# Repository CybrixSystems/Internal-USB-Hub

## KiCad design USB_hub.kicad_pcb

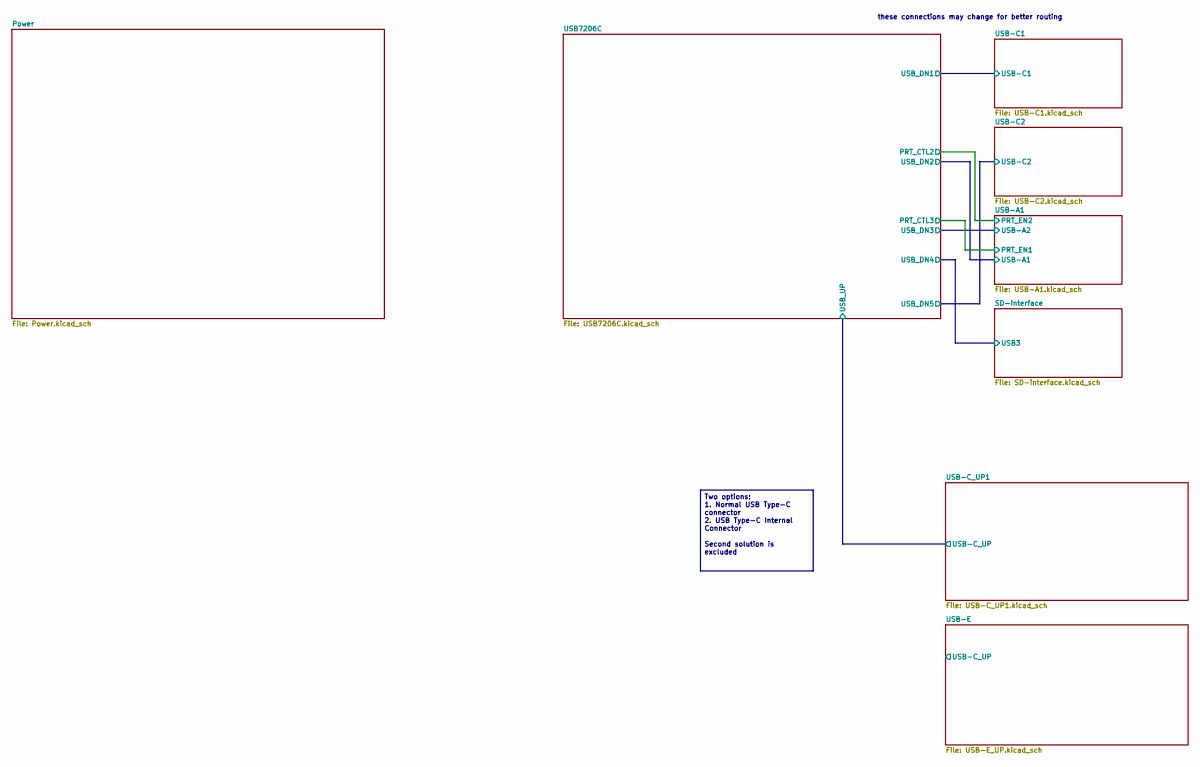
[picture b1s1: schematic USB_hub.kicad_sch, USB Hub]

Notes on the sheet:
these connections may change for better routing
Two options: 1. Normal USB Type-C connector 2. USB Type-C Internal Connector Second solution is excluded

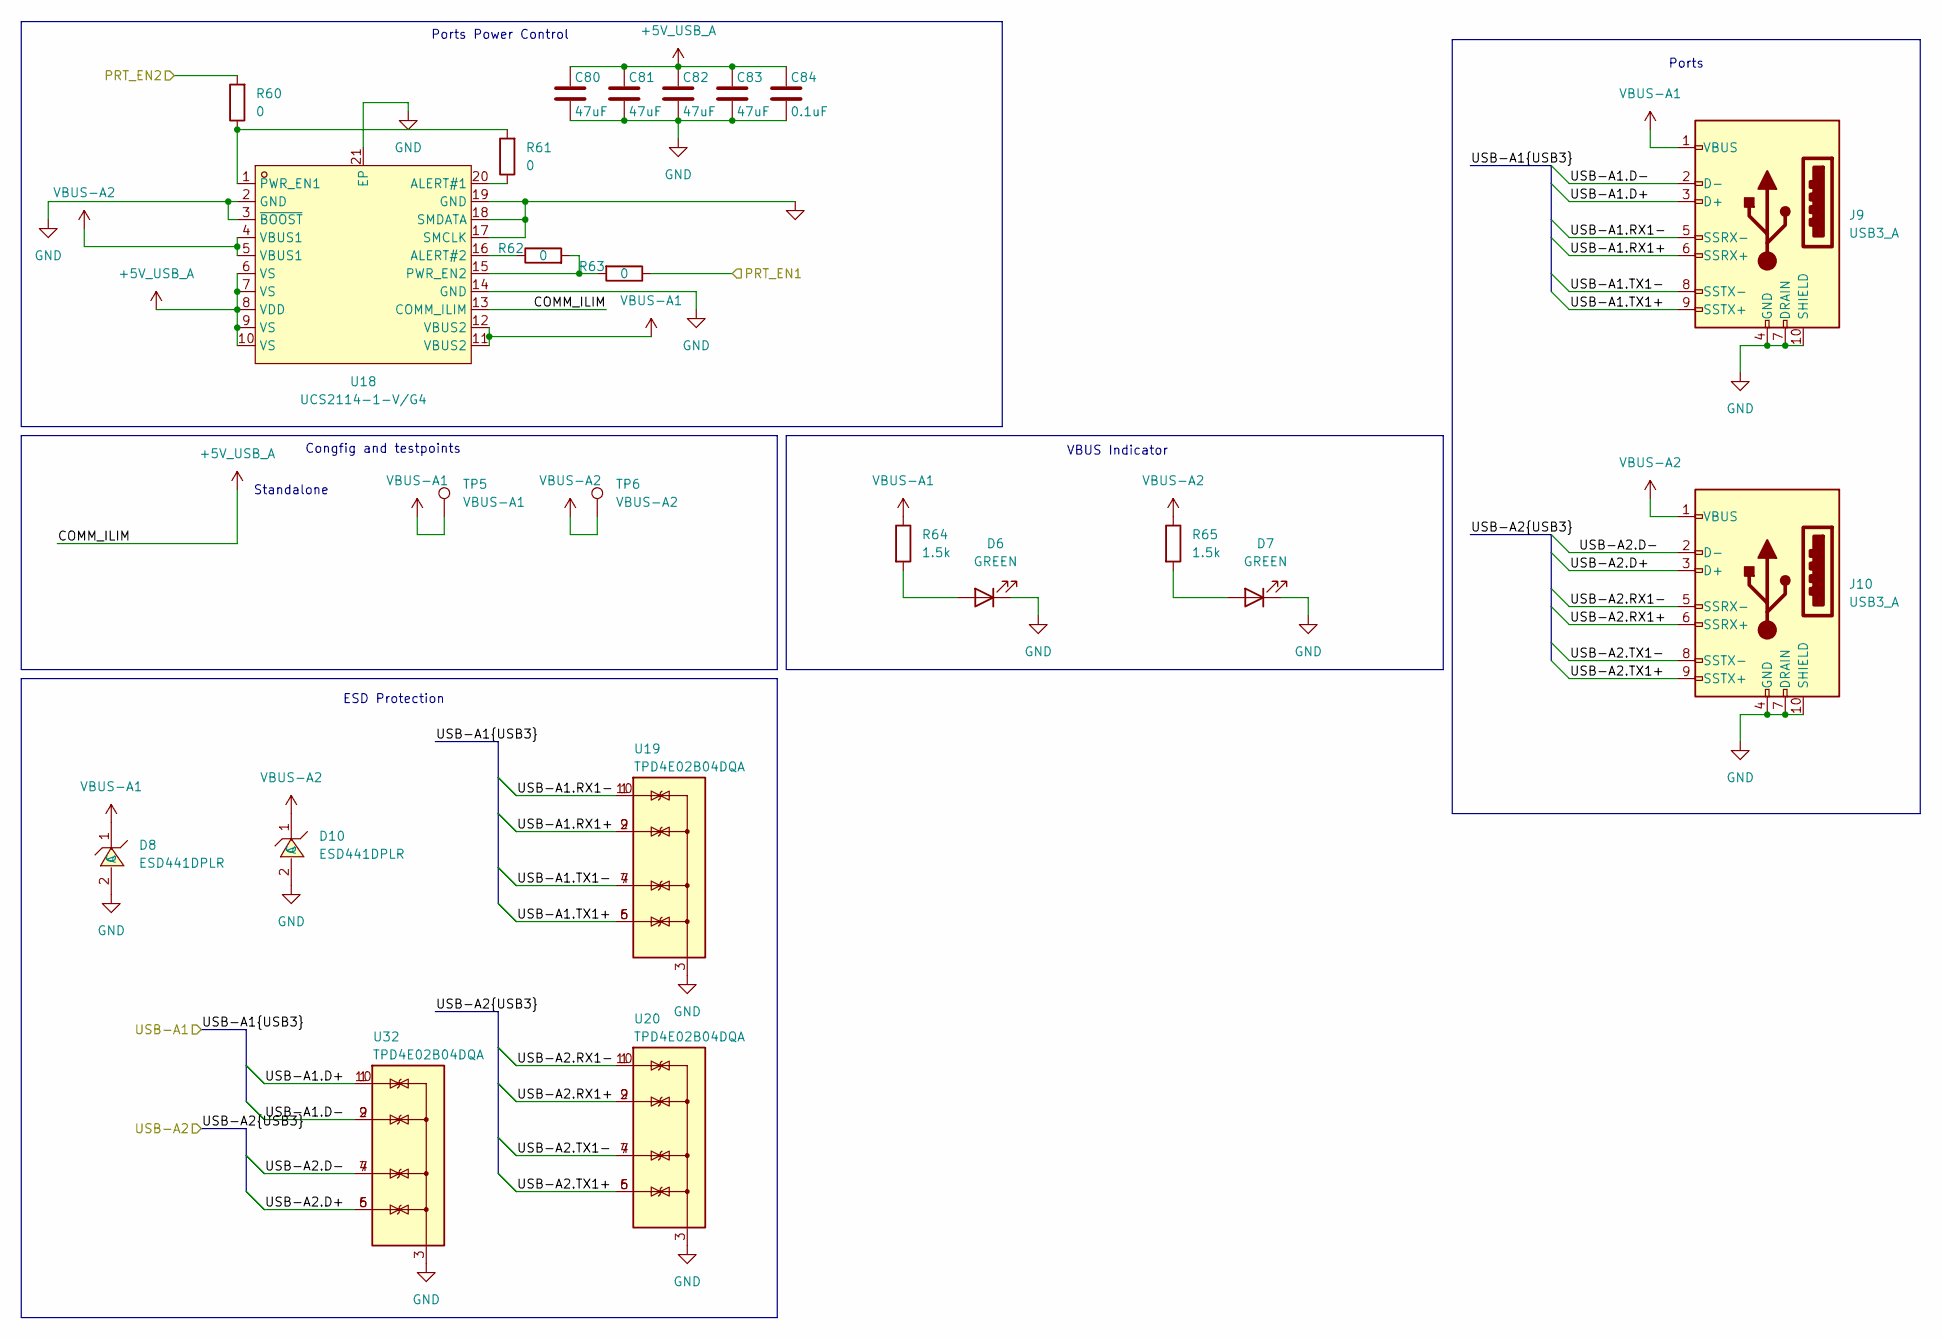
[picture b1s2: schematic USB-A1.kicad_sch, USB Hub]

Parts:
C80, C81, C82, C83: 47uF; C_Radial_D5.0mm_H11.0mm_P2.00mm; LCSC Part C721300
C84: 0.1uF; C_0201_0603Metric; LCSC Part C181043
D6, D7: GREEN; LED_0603_1608Metric; LCSC Part C22371298
D8, D10: ESD441DPLR; X2SON-2_L0.6-W0.3-P0.35; LCSC Part C22427765
J9, J10: USB3_A; GSB4116344HR; LCSC Part C5119948
R60, R61, R62, R63: 0; R_0603_1608Metric; LCSC Part C2906974
R64, R65: 1.5k; R_0402_1005Metric; LCSC Part C327253
TP5: VBUS-A1; TestPoint_Pad_D1.0mm
TP6: VBUS-A2; TestPoint_Pad_D1.0mm
U18: UCS2114-1-V/G4; QFN-20_L4.0-W4.0-P0.50-BL-EP2.7; Mouser Part No 579-UCS2114-1-V/LX; LCSC Part C638222
U19, U20, U32: TPD4E02B04DQA; USON-10_2.5x1.0mm_P0.5mm; LCSC Part C106794

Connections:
+5V_USB_A: C80.1, C81.1, C82.1, C83.1, C84.1, U18.6 (VS), U18.7 (VS), U18.8 (VDD), U18.9 (VS), U18.10 (VS), U18.13 (COMM_ILIM); also elsewhere on the board
/USB-A1/PRT_EN1: R63.1; also elsewhere on the board
/USB-A1/PRT_EN2: R60.2; also elsewhere on the board
/USB-A1/USB-A1.D+: J9.3 (D+), U32.1 (IO1), U32.10 (NC); also elsewhere on the board
/USB-A1/USB-A1.D-: J9.2 (D-), U32.2 (IO2), U32.9 (NC); also elsewhere on the board
/USB-A1/USB-A1.RX1+: J9.6 (SSRX+), U19.2 (IO2), U19.9 (NC); also elsewhere on the board
/USB-A1/USB-A1.RX1-: J9.5 (SSRX-), U19.1 (IO1), U19.10 (NC); also elsewhere on the board
/USB-A1/USB-A1.TX1+: J9.9 (SSTX+), U19.5 (IO4), U19.6 (NC); also elsewhere on the board
/USB-A1/USB-A1.TX1-: J9.8 (SSTX-), U19.4 (IO3), U19.7 (NC); also elsewhere on the board
/USB-A1/USB-A2.D+: J10.3 (D+), U32.5 (IO4), U32.6 (NC); also elsewhere on the board
/USB-A1/USB-A2.D-: J10.2 (D-), U32.4 (IO3), U32.7 (NC); also elsewhere on the board
/USB-A1/USB-A2.RX1+: J10.6 (SSRX+), U20.2 (IO2), U20.9 (NC); also elsewhere on the board
/USB-A1/USB-A2.RX1-: J10.5 (SSRX-), U20.1 (IO1), U20.10 (NC); also elsewhere on the board
/USB-A1/USB-A2.TX1+: J10.9 (SSTX+), U20.5 (IO4), U20.6 (NC); also elsewhere on the board
/USB-A1/USB-A2.TX1-: J10.8 (SSTX-), U20.4 (IO3), U20.7 (NC); also elsewhere on the board
GND: C80.2, C81.2, C82.2, C83.2, C84.2, D6.1 (K), D7.1 (K), D8.2 (A), D10.2 (A), J9.4 (GND), J9.7 (DRAIN), J9.10 (SHIELD), J10.4 (GND), J10.7 (DRAIN), J10.10 (SHIELD), U18.2 (GND), U18.3 (~BOOST), U18.14 (GND), U18.17 (SMCLK), U18.18 (SMDATA), U18.19 (GND), U18.21 (EP), U19.3 (G), U19.8 (G), U20.3 (G), U20.8 (G), U32.3 (G), U32.8 (G); also elsewhere on the board
unnamed: D6.2 (A), R64.2
unnamed: D7.2 (A), R65.2
unnamed: R61.1, U18.20 (ALERT#1)
unnamed: R62.1, U18.16 (ALERT#2)
unnamed: R60.1, R61.2, U18.1 (PWR_EN1)
unnamed: R62.2, R63.2, U18.15 (PWR_EN2)
VBUS-A1: D8.1 (C), J9.1 (VBUS), R64.1, TP5.1, U18.11 (VBUS2), U18.12 (VBUS2)
VBUS-A2: D10.1 (C), J10.1 (VBUS), R65.1, TP6.1, U18.4 (VBUS1), U18.5 (VBUS1)

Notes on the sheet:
ESD Protection
Standalone
Ports
Congfig and testpoints
VBUS Indicator
Ports Power Control

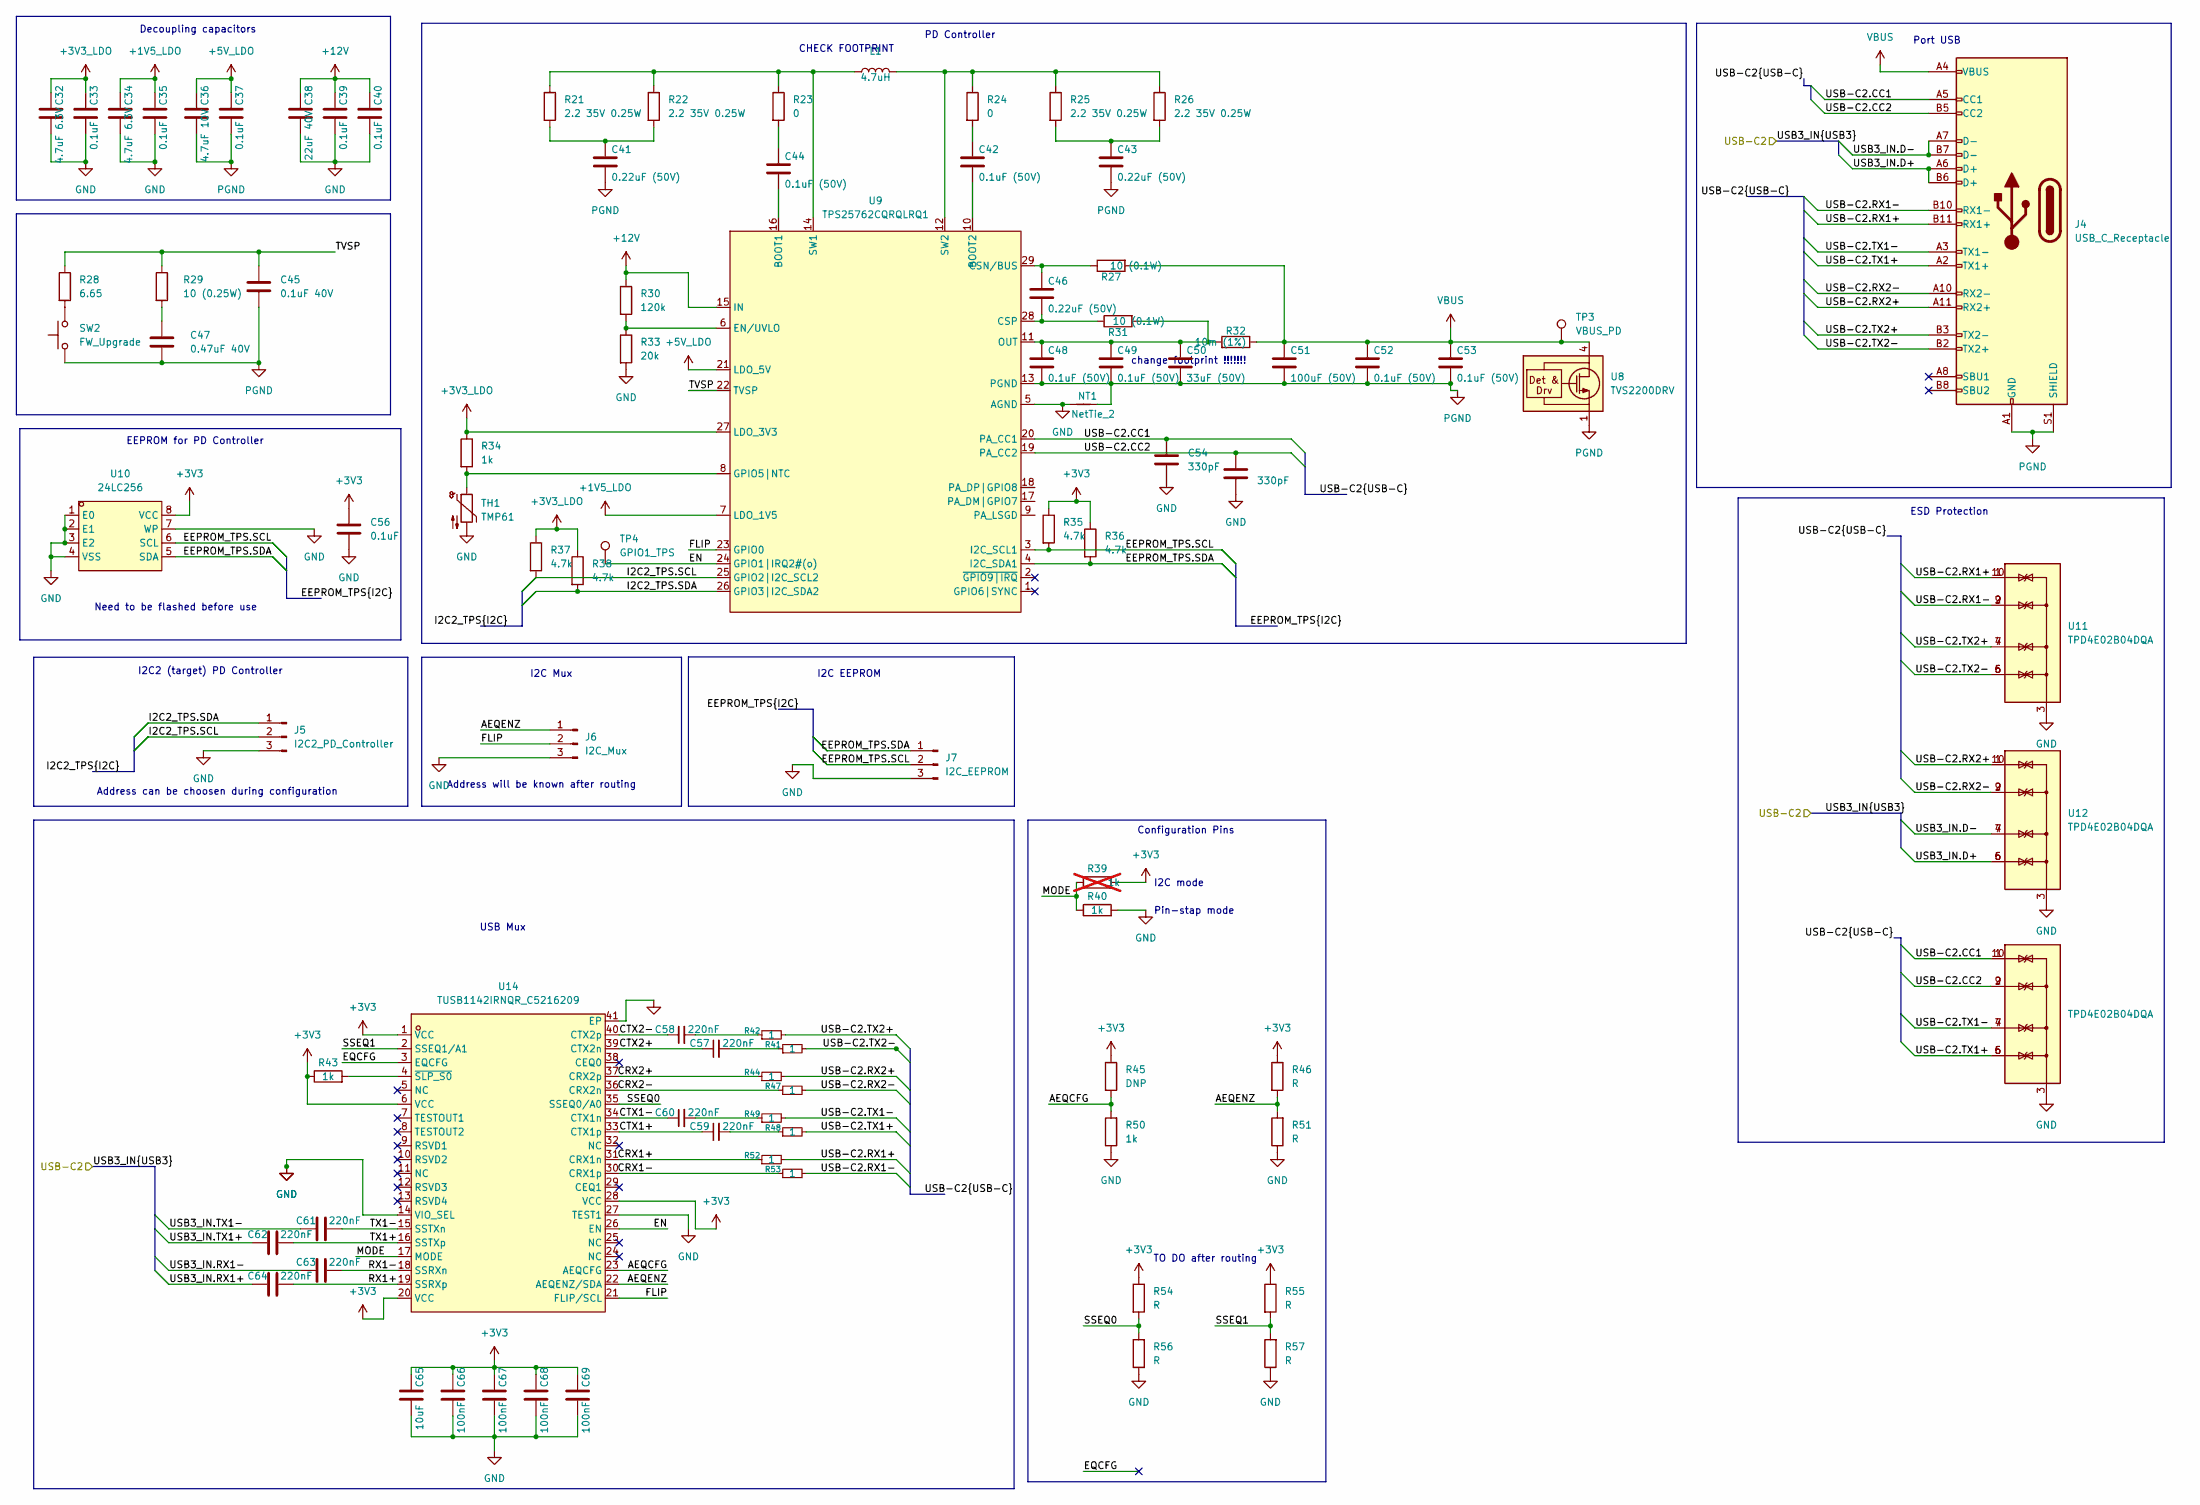
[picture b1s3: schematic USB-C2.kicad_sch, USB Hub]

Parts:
C32, C34: 4.7uF 6.3V; C_0402_1005Metric; LCSC Part C6119944
C33, C35, C37, C39, C40, C56: 0.1uF; C_0201_0603Metric; LCSC Part C181043
C36: 4.7uF 10V; C_0402_1005Metric; LCSC Part C6119944
C38: 22uF 40V; C_1812_4532Metric; LCSC Part C141660
C41, C43, C46: 0.22uF (50V); C_0402_1005Metric; LCSC Part C114401
C42, C44, C48, C49, C52, C53: 0.1uF (50V); C_0402_1005Metric; LCSC Part C5182432
C45: 0.1uF 40V; C_0402_1005Metric; LCSC Part C5182432
C47: 0.47uF 40V; C_0603_1608Metric; LCSC Part C513577
C50: 33uF (50V); C_2220_5750Metric; Mouser Part No 710-865080645010
C51: 100uF (50V); C_Radial_D6.3mm_H11.0mm_P2.50mm; LCSC Part C109392
C54, C55: 330pF; C_0402_1005Metric; LCSC Part C325463
C57, C58, C59, C60, C61, C62, C63, C64: 220nF; C_0201_0603Metric; LCSC Part C701263
C65: 10uF; C_0805_2012Metric; LCSC Part C3039694
C66, C67, C68, C69: 100nF; C_0201_0603Metric; LCSC Part C181043
J4: USB_C_Receptacle; USB420003A; Mouser Part No 640-USB4200-03-A
J5: I2C2_PD_Controller; PinHeader_1x03_P1.00mm_Vertical
J6: I2C_Mux; PinHeader_1x03_P1.00mm_Vertical
J7: I2C_EEPROM; PinHeader_1x03_P1.00mm_Vertical
L1: 4.7uH; L_Coilcraft_XAL1010-XXX; LCSC Part C18199458
NT1: NetTie_2; R_0603_1608Metric
R21, R22, R25, R26: 2.2 35V 0.25W; R_0603_1608Metric; LCSC Part C966185
R23, R24: 0; R_0603_1608Metric; LCSC Part C2906974
R27, R31: 10 (0.1W); R_0603_1608Metric; LCSC Part C510088
R28: 6.65; R_0402_1005Metric; Mouser Part No 71-CRCW04026R65FKEDH; LCSC Part C332644
R29: 10 (0.25W); R_0603_1608Metric; LCSC Part C510088
R30: 120k; R_0402_1005Metric; LCSC Part C93945
R32: 10m (1%); R_2010_5025Metric; LCSC Part C844898
R33: 20k; R_0402_1005Metric; LCSC Part C25765
R34, R40, R43, R50: 1k; R_0402_1005Metric; LCSC Part C11702
R35, R36, R37, R38: 4.7k; R_0402_1005Metric; LCSC Part C105871
R39: 1k; R_0402_1005Metric; LCSC Part C11702; not fitted
R41, R42, R44, R47, R48, R49, R52, R53: 1; R_0201_0603Metric; LCSC Part C469665
R45: DNP; R_0402_1005Metric
R46, R51, R54, R55, R56, R57: R; R_0402_1005Metric
SW2: FW_Upgrade; ultra_small_switch_1.6x3.0mm; LCSC Part C913788
TH1: TMP61; PinHeader_1x02_P1.27mm_Vertical
TP3: VBUS_PD; TestPoint_Pad_D1.0mm
TP4: GPIO1_TPS; TestPoint_Pad_D1.0mm
U8: TVS2200DRV; WSON-6-1EP_2x2mm_P0.65mm_EP1x1.6mm; LCSC Part C523793
U9: TPS25762CQRQLRQ1; VQFN-HR-29_L6.0-W5.0-P0.50_TPS25762CQRQLRQ1; Mouser Part No 595-TPS25762CQRQLRQ1; LCSC Part C5986888
U10: 24LC256; SO-8_L4.9-W3.9-P1.27-LS5.9-BL; LCSC Part C283433
U11, U12, U13: TPD4E02B04DQA; USON-10_2.5x1.0mm_P0.5mm; LCSC Part C106794
U14: TUSB1142IRNQR_C5216209; WQFN-40_L6.0-W4.0-P0.40-TL-EP; LCSC Part C5216209

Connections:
+1V5_LDO: C34.1, C35.1, U9.7 (LDO_1V5)
+3V3: C56.1, C65.1, C66.1, C67.1, C68.1, C69.1, R35.1, R36.1, R39.2, R43.1, R45.1, R46.1, R54.1, R55.1, U10.8 (VCC), U14.1 (VCC), U14.6 (VCC), U14.20 (VCC), U14.28 (VCC); also elsewhere on the board
+3V3_LDO: C32.1, C33.1, R34.1, R37.1, R38.1, U9.27 (LDO_3V3)
+5V_LDO: C36.1, C37.1, U9.21 (LDO_5V)
+12V: C38.1, C39.1, C40.1, R30.1, U9.15 (IN); also elsewhere on the board
/USB-C2/AEQCFG: R45.2, R50.2, U14.23 (AEQCFG)
/USB-C2/AEQENZ: J6.1, R46.2, R51.2, U14.22 (AEQENZ/SDA)
/USB-C2/CRX1+: R52.1, U14.31 (CRX1n)
/USB-C2/CRX1-: R53.1, U14.30 (CRX1p)
/USB-C2/CRX2+: R44.1, U14.37 (CRX2p)
/USB-C2/CRX2-: R47.1, U14.36 (CRX2n)
/USB-C2/CTX1+: C59.1, U14.33 (CTX1p)
/USB-C2/CTX1-: C60.1, U14.34 (CTX1n)
/USB-C2/CTX2+: C57.1, U14.39 (CTX2n)
/USB-C2/CTX2-: C58.1, U14.40 (CTX2p)
/USB-C2/EEPROM_TPS.SCL: J7.2, R35.2, U9.3 (I2C_SCL1), U10.6 (SCL)
/USB-C2/EEPROM_TPS.SDA: J7.1, R36.2, U9.4 (I2C_SDA1), U10.5 (SDA)
/USB-C2/EN: TP4.1, U9.24 (GPIO1|IRQ2#(o)), U14.26 (EN)
/USB-C2/EQCFG: U14.3 (EQCFG)
/USB-C2/FLIP: J6.2, U9.23 (GPIO0), U14.21 (FLIP/SCL)
/USB-C2/I2C2_TPS.SCL: J5.2, R37.2, U9.25 (GPIO2|I2C_SCL2)
/USB-C2/I2C2_TPS.SDA: J5.1, R38.2, U9.26 (GPIO3|I2C_SDA2)
/USB-C2/MODE: R39.1, R40.1, U14.17 (MODE)
/USB-C2/RX1+: C64.2, U14.19 (SSRXp)
/USB-C2/RX1-: C63.2, U14.18 (SSRXn)
/USB-C2/SSEQ0: R54.2, R56.2, U14.35 (SSEQ0/A0)
/USB-C2/SSEQ1: R55.2, R57.2, U14.2 (SSEQ1/A1)
/USB-C2/TVSP: C45.1, R28.1, R29.1, U9.22 (TVSP)
/USB-C2/TX1+: C62.2, U14.16 (SSTXp)
/USB-C2/TX1-: C61.2, U14.15 (SSTXn)
/USB-C2/USB3_IN.D+: J4.A6 (D+), J4.B6 (D+), U12.5 (IO4), U12.6 (NC); also elsewhere on the board
/USB-C2/USB3_IN.D-: J4.A7 (D-), J4.B7 (D-), U12.4 (IO3), U12.7 (NC); also elsewhere on the board
/USB-C2/USB3_IN.RX1+: C64.1; also elsewhere on the board
/USB-C2/USB3_IN.RX1-: C63.1; also elsewhere on the board
/USB-C2/USB3_IN.TX1+: C62.1; also elsewhere on the board
/USB-C2/USB3_IN.TX1-: C61.1; also elsewhere on the board
/USB-C2/USB-C2.CC1: C54.1, J4.A5 (CC1), U9.20 (PA_CC1), U13.1 (IO1), U13.10 (NC)
/USB-C2/USB-C2.CC2: C55.1, J4.B5 (CC2), U9.19 (PA_CC2), U13.2 (IO2), U13.9 (NC)
/USB-C2/USB-C2.RX1+: J4.B11 (RX1+), R52.2, U11.1 (IO1), U11.10 (NC)
/USB-C2/USB-C2.RX1-: J4.B10 (RX1-), R53.2, U11.2 (IO2), U11.9 (NC)
/USB-C2/USB-C2.RX2+: J4.A11 (RX2+), R44.2, U12.1 (IO1), U12.10 (NC)
/USB-C2/USB-C2.RX2-: J4.A10 (RX2-), R47.2, U12.2 (IO2), U12.9 (NC)
/USB-C2/USB-C2.TX1+: J4.A2 (TX1+), R48.2, U13.5 (IO4), U13.6 (NC)
/USB-C2/USB-C2.TX1-: J4.A3 (TX1-), R49.2, U13.4 (IO3), U13.7 (NC)
/USB-C2/USB-C2.TX2+: J4.B3 (TX2-), R42.2, U11.4 (IO3), U11.7 (NC)
/USB-C2/USB-C2.TX2-: J4.B2 (TX2+), R41.2, U11.5 (IO4), U11.6 (NC)
GND: C32.2, C33.2, C34.2, C35.2, C38.2, C39.2, C40.2, C54.2, C55.2, C56.2, C65.2, C66.2, C67.2, C68.2, C69.2, J5.3, J6.3, J7.3, NT1.1, R33.2, R40.2, R50.1, R51.1, R56.1, R57.1, TH1.2, U9.5 (AGND), U10.1 (E0), U10.2 (E1), U10.3 (E2), U10.4 (VSS), U10.7 (WP), U11.3 (G), U11.8 (G), U12.3 (G), U12.8 (G), U13.3 (G), U13.8 (G), U14.14 (VIO_SEL), U14.27 (TEST1), U14.41 (EP); also elsewhere on the board
unnamed: C41.1, R21.2, R22.2
unnamed: C42.1, R24.2
unnamed: C43.1, R25.2, R26.2
unnamed: C44.1, R23.2
unnamed: C47.1, R29.2
unnamed: C57.2, R41.1
unnamed: C58.2, R42.1
unnamed: C59.2, R48.1
unnamed: C60.2, R49.1
unnamed: R28.2, SW2.2
unnamed: C44.2, U9.16 (BOOT1)
unnamed: C42.2, U9.10 (BOOT2)
unnamed: C46.1, R27.1, U9.29 (CSN/BUS)
unnamed: C46.2, R31.1, U9.28 (CSP)
unnamed: R30.2, R33.1, U9.6 (EN/UVLO)
unnamed: R34.2, TH1.1, U9.8 (GPIO5|NTC)
unnamed: C48.1, C49.1, C50.1, R31.2, R32.2, U9.11 (OUT)
unnamed: L1.1, R21.1, R22.1, R23.1, U9.14 (SW1)
unnamed: L1.2, R24.1, R25.1, R26.1, U9.12 (SW2)
unnamed: R43.2, U14.4 (~SLP_S0)
PGND: C36.2, C37.2, C41.2, C43.2, C45.2, C47.2, C48.2, C49.2, C50.2, C51.2, C52.2, C53.2, J4.A1 (GND), J4.A12 (GND), J4.B1 (GND), J4.B12 (GND), J4.S1 (SHIELD), NT1.2, SW2.1, U8.1 (GND), U8.2 (GND), U8.3 (GND), U8.7 (GND), U9.13 (PGND)
VBUS: C51.1, C52.1, C53.1, J4.A4 (VBUS), J4.A9 (VBUS), J4.B4 (VBUS), J4.B9 (VBUS), R27.2, R32.1, TP3.1, U8.4 (IN), U8.5 (IN), U8.6 (IN)

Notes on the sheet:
TO DO after routing
I2C2 (target) PD Controller
EEPROM for PD Controller
Address will be known after routing
Address can be choosen during configuration
Configuration Pins
USB Mux
Decoupling capacitors
I2C mode
CHECK FOOTPRINT
PD Controller
Pin-stap mode
I2C EEPROM
Port USB
ESD Protection
Need to be flashed before use
I2C Mux
change footprint !!!!!!!

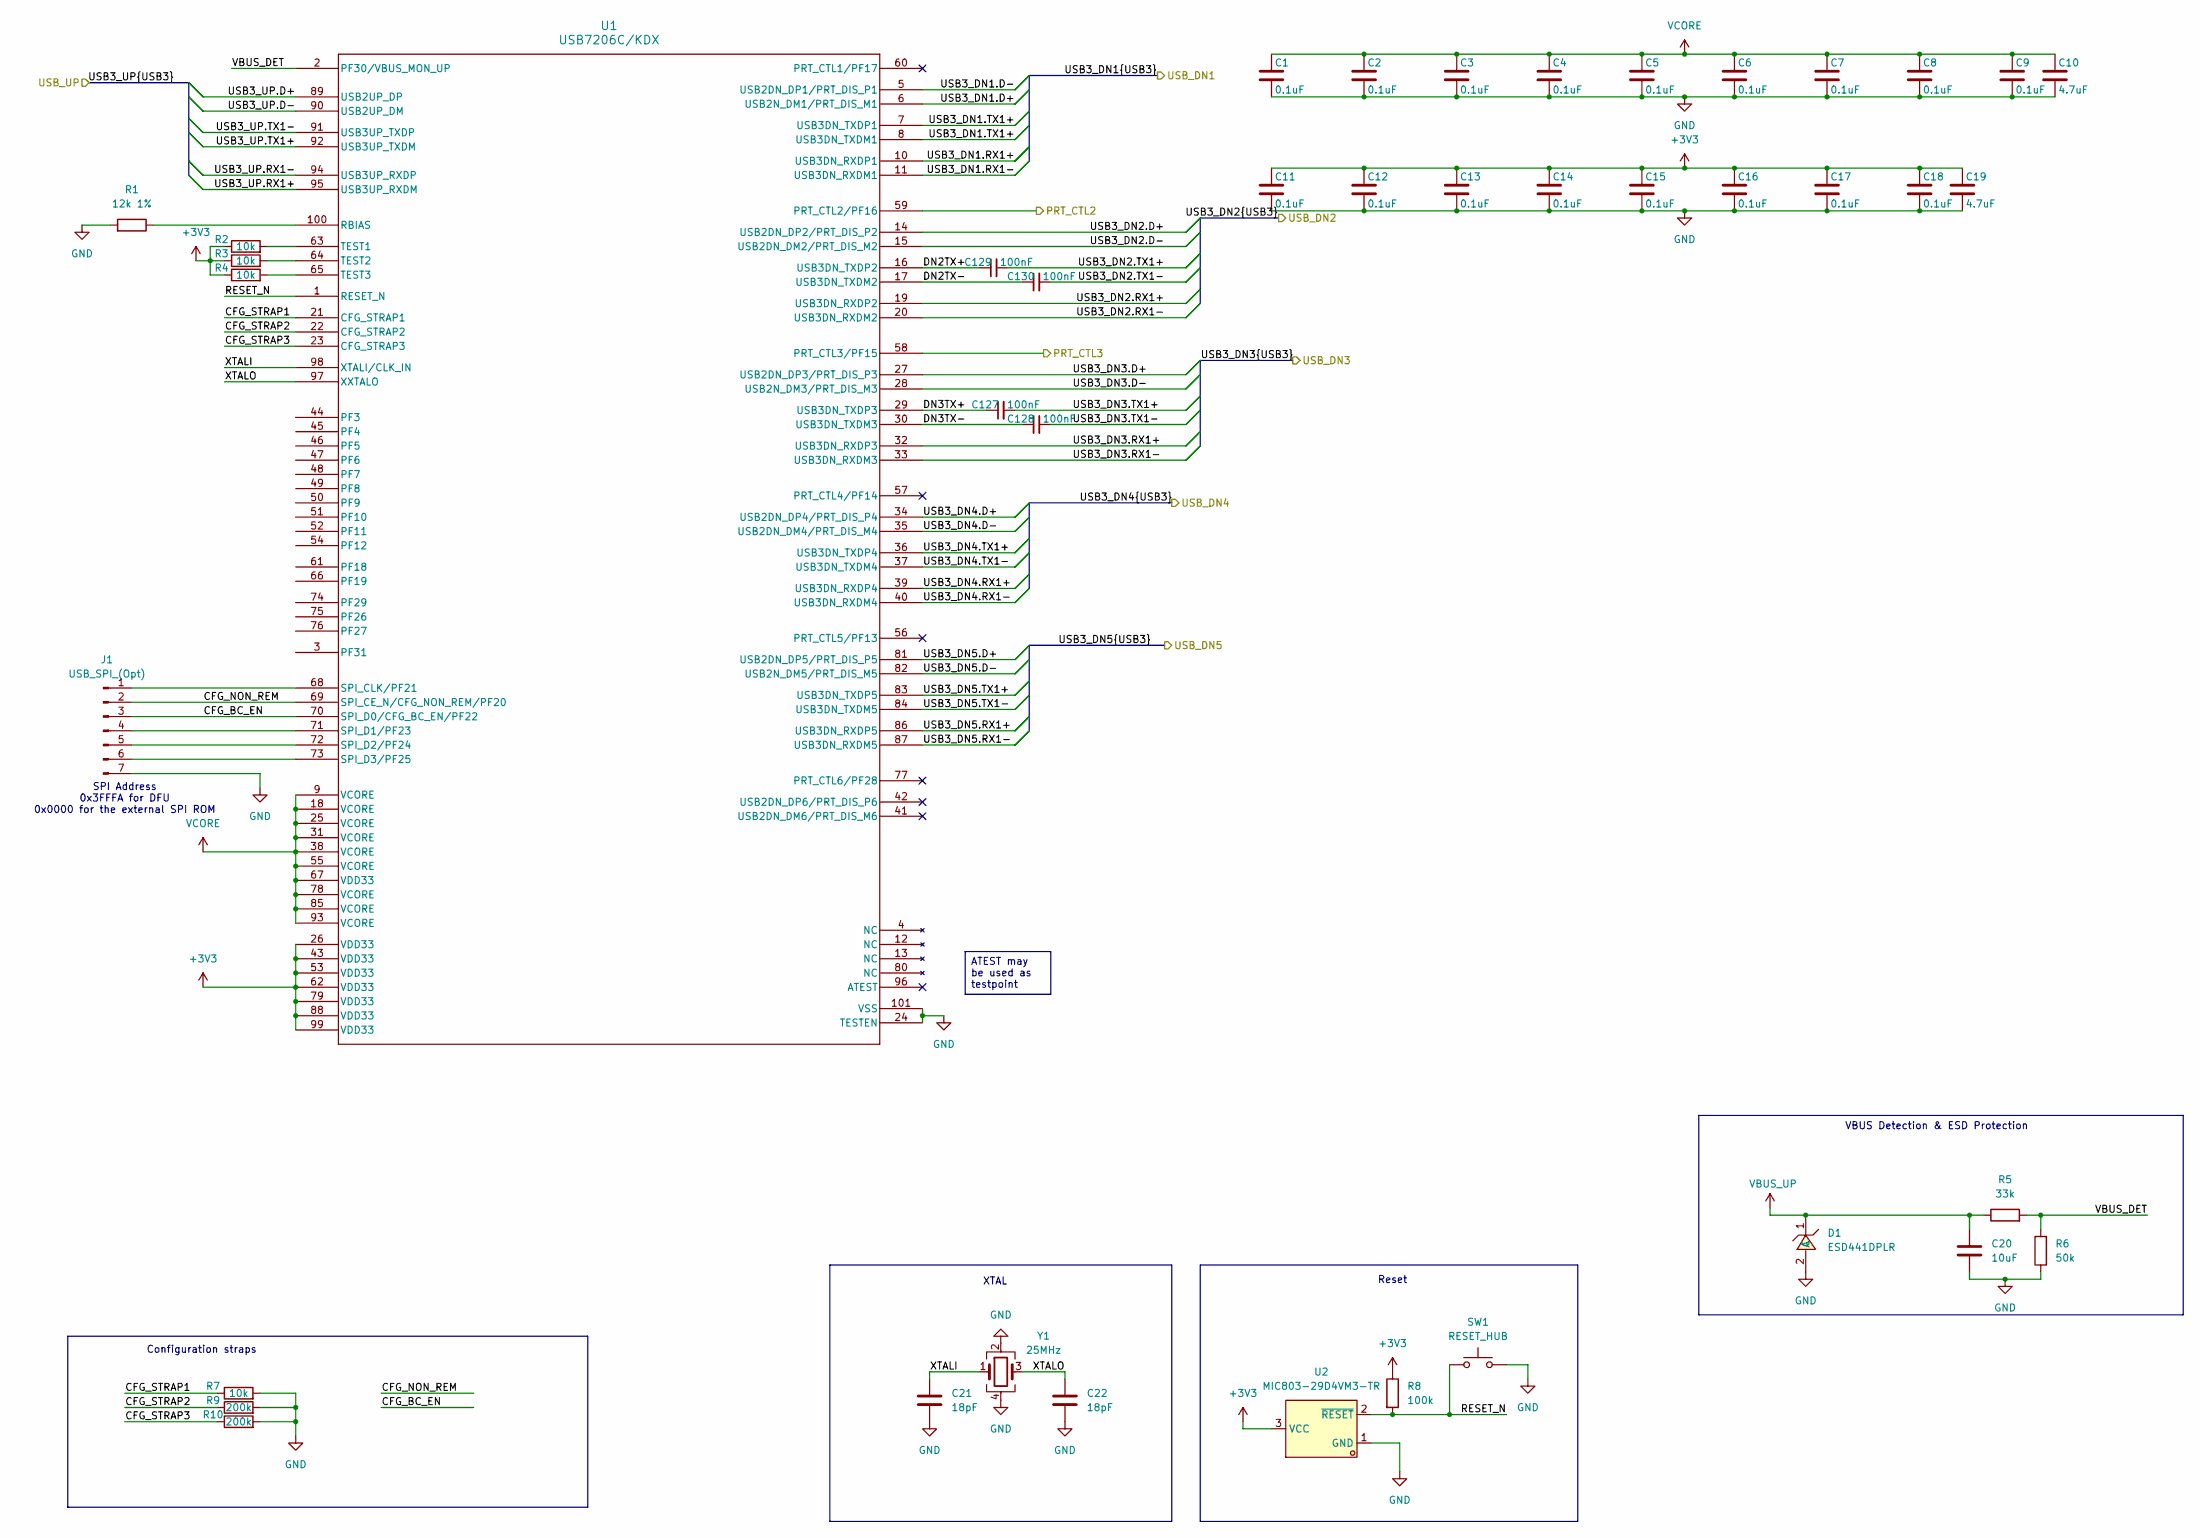
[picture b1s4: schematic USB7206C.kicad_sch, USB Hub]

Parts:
C1, C2, C3, C4, C5, C6, C7, C8, C9, C11, C12, C13, C14, C15, C16, C17, C18: 0.1uF; C_0201_0603Metric; LCSC Part C181043
C10, C19: 4.7uF; C_0805_2012Metric; LCSC Part C6119944
C20: 10uF; C_0805_2012Metric; LCSC Part C3039694
C21, C22: 18pF; C_0402_1005Metric; LCSC Part C33149
C127, C128, C129, C130: 100nF; C_0201_0603Metric; LCSC Part C181043
D1: ESD441DPLR; X2SON-2_L0.6-W0.3-P0.35; LCSC Part C22427765
J1: USB_SPI_(Opt); PinHeader_1x03_P1.00mm_Vertical
R1: 12k 1%; R_0402_1005Metric; LCSC Part C102781
R2, R3, R4, R7: 10k; R_0402_1005Metric; LCSC Part C25744
R5: 33k; R_0402_1005Metric; LCSC Part C25779
R6: 50k; R_0402_1005Metric; LCSC Part C166559
R8: 100k; R_0402_1005Metric; LCSC Part C25741
R9, R10: 200k; R_0402_1005Metric; LCSC Part C25764
SW1: RESET_HUB; ultra_small_switch_1.6x3.0mm; LCSC Part C913788
U1: USB7206C/KDX; QFN40P1200X1200X90-101N-D; Mouser Part No 579-USB7206C/KDX
U2: MIC803-29D4VM3-TR; SOT-23-3_L2.9-W1.3-P1.90-LS2.4-BR; LCSC Part C626154
Y1: 25MHz; Crystal_SMD_3225-4Pin_3.2x2.5mm; LCSC Part C179643

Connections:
+3V3: C11.1, C12.1, C13.1, C14.1, C15.1, C16.1, C17.1, C18.1, C19.1, R2.1, R3.1, R4.1, R8.1, U1.26 (VDD33), U1.43 (VDD33), U1.53 (VDD33), U1.62 (VDD33), U1.79 (VDD33), U1.88 (VDD33), U1.99 (VDD33), U2.3 (VCC); also elsewhere on the board
/SD-interface/USB-SD.D+: U1.34 (USB2DN_DP4/PRT_DIS_P4); also elsewhere on the board
/SD-interface/USB-SD.D-: U1.35 (USB2DN_DM4/PRT_DIS_M4); also elsewhere on the board
/SD-interface/USB-SD.RX1+: U1.39 (USB3DN_RXDP4); also elsewhere on the board
/SD-interface/USB-SD.RX1-: U1.40 (USB3DN_RXDM4); also elsewhere on the board
/SD-interface/USB-SD.TX1+: U1.36 (USB3DN_TXDP4); also elsewhere on the board
/SD-interface/USB-SD.TX1-: U1.37 (USB3DN_TXDM4); also elsewhere on the board
/USB7206C/CFG_BC_EN: J1.3, U1.70 (SPI_D0/CFG_BC_EN/PF22)
/USB7206C/CFG_NON_REM: J1.2, U1.69 (SPI_CE_N/CFG_NON_REM/PF20)
/USB7206C/CFG_STRAP1: R7.1, U1.21 (CFG_STRAP1)
/USB7206C/CFG_STRAP2: R9.1, U1.22 (CFG_STRAP2)
/USB7206C/CFG_STRAP3: R10.1, U1.23 (CFG_STRAP3)
/USB7206C/DN2TX+: C129.1, U1.16 (USB3DN_TXDP2)
/USB7206C/DN2TX-: C130.1, U1.17 (USB3DN_TXDM2)
/USB7206C/DN3TX+: C127.1, U1.29 (USB3DN_TXDP3)
/USB7206C/DN3TX-: C128.1, U1.30 (USB3DN_TXDM3)
/USB7206C/RESET_N: R8.2, SW1.1, U1.1 (RESET_N), U2.2 (~RESET)
/USB7206C/VBUS_DET: R5.2, R6.2, U1.2 (PF30/VBUS_MON_UP)
/USB7206C/XTALI: C21.2, U1.98 (XTALI/CLK_IN), Y1.1
/USB7206C/XTALO: C22.2, U1.97 (XXTALO), Y1.3
/USB-A1/PRT_EN1: U1.58 (PRT_CTL3/PF15); also elsewhere on the board
/USB-A1/PRT_EN2: U1.59 (PRT_CTL2/PF16); also elsewhere on the board
/USB-A1/USB-A1.D+: U1.14 (USB2DN_DP2/PRT_DIS_P2); also elsewhere on the board
/USB-A1/USB-A1.D-: U1.15 (USB2DN_DM2/PRT_DIS_M2); also elsewhere on the board
/USB-A1/USB-A1.RX1+: U1.19 (USB3DN_RXDP2); also elsewhere on the board
/USB-A1/USB-A1.RX1-: U1.20 (USB3DN_RXDM2); also elsewhere on the board
/USB-A1/USB-A1.TX1+: C129.2; also elsewhere on the board
/USB-A1/USB-A1.TX1-: C130.2; also elsewhere on the board
/USB-A1/USB-A2.D+: U1.27 (USB2DN_DP3/PRT_DIS_P3); also elsewhere on the board
/USB-A1/USB-A2.D-: U1.28 (USB2N_DM3/PRT_DIS_M3); also elsewhere on the board
/USB-A1/USB-A2.RX1+: U1.32 (USB3DN_RXDP3); also elsewhere on the board
/USB-A1/USB-A2.RX1-: U1.33 (USB3DN_RXDM3); also elsewhere on the board
/USB-A1/USB-A2.TX1+: C127.2; also elsewhere on the board
/USB-A1/USB-A2.TX1-: C128.2; also elsewhere on the board
/USB-C1/USB3_IN.D+: U1.6 (USB2N_DM1/PRT_DIS_M1); also elsewhere on the board
/USB-C1/USB3_IN.D-: U1.5 (USB2DN_DP1/PRT_DIS_P1); also elsewhere on the board
/USB-C1/USB3_IN.RX1+: U1.10 (USB3DN_RXDP1); also elsewhere on the board
/USB-C1/USB3_IN.RX1-: U1.11 (USB3DN_RXDM1); also elsewhere on the board
/USB-C1/USB3_IN.TX1+: U1.7 (USB3DN_TXDP1), U1.8 (USB3DN_TXDM1); also elsewhere on the board
/USB-C2/USB3_IN.D+: U1.81 (USB2DN_DP5/PRT_DIS_P5); also elsewhere on the board
/USB-C2/USB3_IN.D-: U1.82 (USB2N_DM5/PRT_DIS_M5); also elsewhere on the board
/USB-C2/USB3_IN.RX1+: U1.86 (USB3DN_RXDP5); also elsewhere on the board
/USB-C2/USB3_IN.RX1-: U1.87 (USB3DN_RXDM5); also elsewhere on the board
/USB-C2/USB3_IN.TX1+: U1.83 (USB3DN_TXDP5); also elsewhere on the board
/USB-C2/USB3_IN.TX1-: U1.84 (USB3DN_TXDM5); also elsewhere on the board
/USB-C_UP1/USB3_IN.D+: U1.89 (USB2UP_DP); also elsewhere on the board
/USB-C_UP1/USB3_IN.D-: U1.90 (USB2UP_DM); also elsewhere on the board
/USB-C_UP1/USB3_IN.RX1+: U1.95 (USB3UP_RXDM); also elsewhere on the board
/USB-C_UP1/USB3_IN.RX1-: U1.94 (USB3UP_RXDP); also elsewhere on the board
/USB-C_UP1/USB3_IN.TX1+: U1.92 (USB3UP_TXDM); also elsewhere on the board
/USB-C_UP1/USB3_IN.TX1-: U1.91 (USB3UP_TXDP); also elsewhere on the board
GND: C1.2, C2.2, C3.2, C4.2, C5.2, C6.2, C7.2, C8.2, C9.2, C10.2, C11.2, C12.2, C13.2, C14.2, C15.2, C16.2, C17.2, C18.2, C19.2, C20.2, C21.1, C22.1, D1.2 (A), J1.7, R1.2, R6.1, R7.2, R9.2, R10.2, SW1.2, U1.24 (TESTEN), U1.101 (VSS), U2.1 (GND), Y1.2, Y1.4; also elsewhere on the board
unnamed: J1.1, U1.68 (SPI_CLK/PF21)
unnamed: J1.4, U1.71 (SPI_D1/PF23)
unnamed: J1.5, U1.72 (SPI_D2/PF24)
unnamed: J1.6, U1.73 (SPI_D3/PF25)
unnamed: R1.1, U1.100 (RBIAS)
unnamed: R2.2, U1.63 (TEST1)
unnamed: R3.2, U1.64 (TEST2)
unnamed: R4.2, U1.65 (TEST3)
VBUS_UP: C20.1, D1.1 (C), R5.1; also elsewhere on the board
VCORE: C1.1, C2.1, C3.1, C4.1, C5.1, C6.1, C7.1, C8.1, C9.1, C10.1, U1.9 (VCORE), U1.18 (VCORE), U1.25 (VCORE), U1.31 (VCORE), U1.38 (VCORE), U1.55 (VCORE), U1.67 (VDD33), U1.78 (VCORE), U1.85 (VCORE), U1.93 (VCORE); also elsewhere on the board

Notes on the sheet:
Configuration straps
SPI Address 0x3FFFA for DFU 0x0000 for the external SPI ROM
VBUS Detection & ESD Protection
XTAL
Reset
ATEST may be used as testpoint

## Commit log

2025-08-04 project upload
2025-08-04 labels naming fixes, USB Type E connector added
2025-08-04 Port Power Control added to USB7206C schematics
2025-08-07 TPS25762 EEPROM connector added
2025-08-10 Create LICENSE
    Added LICENSE file with CERN-OHL-P license
2025-08-11 deleted duplicated capacitor
2025-08-11 Footprint assigned to symbols and transfer to pcb
2025-08-13 footprints grouped by the function
2025-08-13 Minor fixes
    Fixed unclear labelling of buses
2025-08-14 Scheme fixes
    Fixed wrong connection of SNS pin of U21
    USB7206c symbol improved
    R7's value fixed
2025-08-20 MCP19035 changed to MP8795
    TPS7A4701xRGW to AP7361C-33E
    Led Indicator added
2025-08-21 Added documentation of ICs
2025-08-21 I2C Addresses added to scheme
2025-08-22 eFuse added
2025-08-24 Ferrite Breads added for 5V, TVS and ESD diodes added
2025-08-24 Ferrite bread filter for LDO and MIC23201, labelling improved
2025-08-24 GL3224 datasheet added
2025-08-24 Scheme pdf generated
2025-08-24 Schematic reannotated
2025-08-24 Q1 changed to MMBT2222A
2025-08-24 J11 changed to 8-pin PCIe connector, footprint assigned
2025-08-24 footprints assigned, U21 change to SiRA80DP
2025-08-25 Values of C105 and R81 corrected
2025-08-25 Board set-up setted, Scheme pdf exported,
2025-08-25 Net class for USB SS signals created and applied on schematic
2025-08-25 Net class label fixed on page 4
2025-08-25 Next net class label fixes, swap of the SS lines for better routing
2025-08-25 scheme regenerated
2025-08-26 Added lcsc part number for most of components, fixes for better routing
2025-08-26 Added application notes to docs folder
2025-08-27 Added lcsc part number for most of resistors
2025-08-27 Corrected calculations of MP8795's external components
2025-08-28 minor schematic fixes, footprints changes, layout improvements
2025-08-29 comments to schematic added, changed a few components
2025-08-29 STEP file generated
2025-09-01 AP7361C'sOO footprint changed, Inductors footprint improved
2025-09-02 Rearrange of the component placement, scheme changes for better routing
2025-09-02 board outline repaired, 3d model and schematic exported
